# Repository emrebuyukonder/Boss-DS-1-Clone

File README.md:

# Boss DS-1 Distortion Clone (Custom Build) - Outdated

## About The Project

This repository contains the schematic, PCB design files, and build documentation for a custom-built clone of the legendary Boss DS-1 Distortion pedal. Designed from the ground up using **KiCad**, this project aims to faithfully recreate the iconic hard-clipping distortion tone while implementing modern hardware practices such as True Bypass switching and optimized component routing.

## Key Features & Modifications

While the core audio path remains true to the original DS-1 architecture, several mechanical and component-level modifications were made based on the local availability of certain original components and hardware.

* **Custom Transistor Selection:** The original BC549C transistors were substituted with **JC2N3904S49 (NPN)** transistors for the input buffer (Q1), gain boost (Q2), and output buffer (Q3) stages. The PCB footprints were carefully matched to accommodate the E-B-C pinout of the 2N3904.
* **True Bypass Switching:** Unlike the original Boss buffered bypass, this build utilizes a **3PDT 9-Pin Latching Footswitch**. This ensures zero tone coloration when the pedal is disengaged and includes an independent pole for the status LED.
* **Smart Power Management:** Integrated a Stereo Input Jack to act as a ground-shunt switch. The 9V battery is completely disconnected from the circuit when the input cable is unplugged, preserving battery life.
* **Capacitor Accuracy:** High-quality film and ceramic capacitors are used throughout the tone stack and filtering stages (e.g., precise 100pF and 220pF ceramics for RF filtering in the op-amp feedback loop).

## Tools & Technologies Used

* **EDA Software:** KiCad (Schematic Capture & PCB Layout)
* **Testing & Measurement:** UNI-T UT33D+ Digital Multimeter
* **Audio Components:** 1/4" Mono/Stereo Jacks, Custom PCB.

## Hardware Wiring Guide

Proper off-board wiring is critical for a noise-free pedal. Here is the standard implementation used in this build:

* **Input Jack (Stereo):**
   * *Tip:* Routed to 3PDT Switch (Input).
    * *Ring:* Connected to the 9V Battery Negative (Black wire).
    * *Sleeve:* Connected to System Ground (Star Grounding).
* **Output Jack (Mono):**
    * *Tip:* Routed from 3PDT Switch (Output).
    * *Sleeve:* Connected to System Ground.

## Author

Designed and built by **Erdoğan Emre Büyükönder** (Music Producer / Composer under the pseudonym *Magnus Dux*). 

As an Electrical-Electronics Engineering student and a music producer, this project bridges the gap between theoretical circuit analysis and practical, stage-ready audio equipment.

---
*Note: The "Boss" and "DS-1" names are trademarks of Roland Corporation. This project is strictly for educational purposes and personal use.*

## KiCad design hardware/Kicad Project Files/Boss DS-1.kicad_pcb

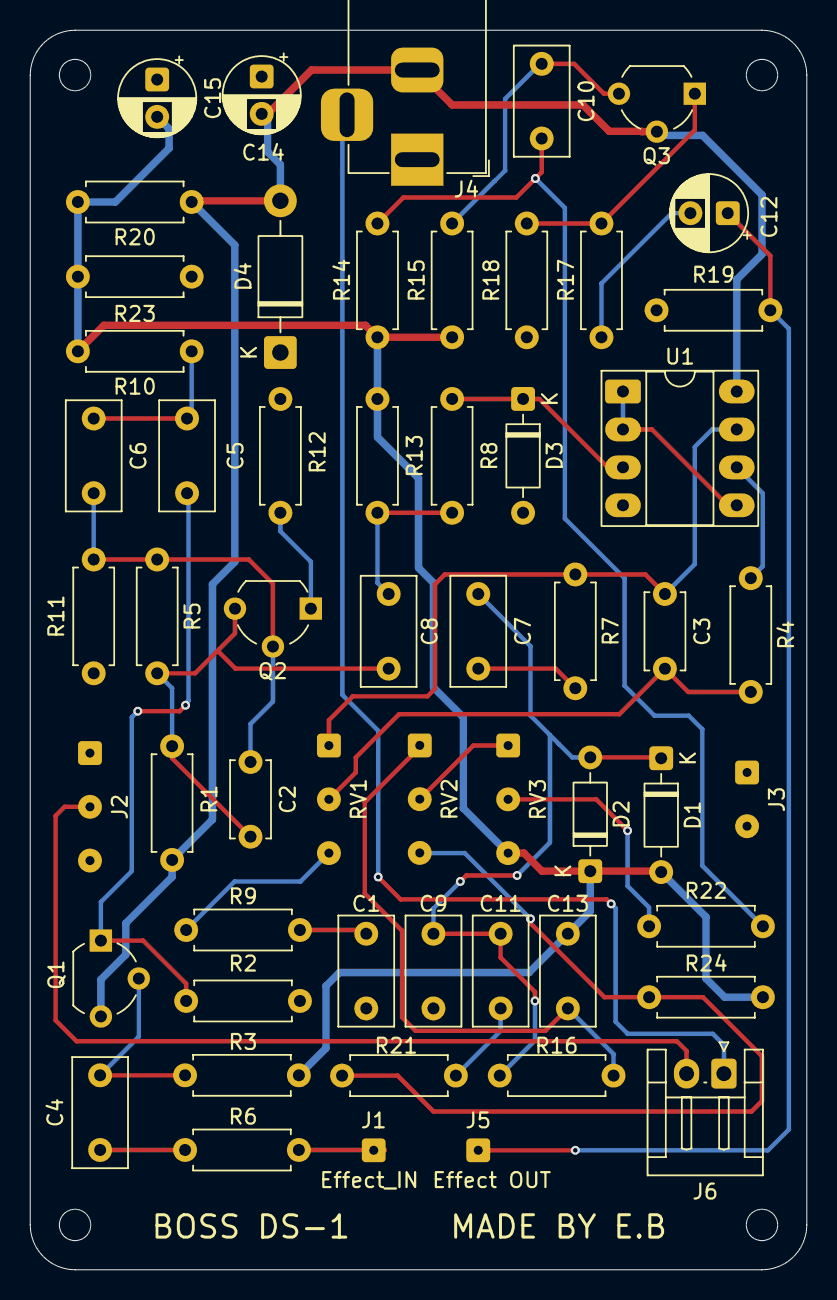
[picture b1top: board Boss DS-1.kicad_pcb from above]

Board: 2 copper layers, 52.0 x 83.0 mm, 56 parts (0 on the bottom side), 33 nets.

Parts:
C1, C5, C7: 0.47u; C_Rect_L7.2mm_W3.5mm_P5.00mm_FKS2_FKP2_MKS2_MKP2
C2: 250p; C_Disc_D5.0mm_W2.5mm_P5.00mm
C3: 100p; C_Disc_D5.0mm_W2.5mm_P5.00mm
C4, C6: 47n; C_Rect_L7.2mm_W3.5mm_P5.00mm_FKS2_FKP2_MKS2_MKP2
C8: 68n; C_Rect_L7.2mm_W3.5mm_P5.00mm_FKS2_FKP2_MKS2_MKP2
C9: 0.01u; C_Rect_L7.2mm_W3.5mm_P5.00mm_FKS2_FKP2_MKS2_MKP2
C10: 0.047u; C_Rect_L7.2mm_W3.5mm_P5.00mm_FKS2_FKP2_MKS2_MKP2
C11: 0.022u; C_Rect_L7.2mm_W3.5mm_P5.00mm_FKS2_FKP2_MKS2_MKP2
C12: 1u; CP_Radial_D5.0mm_P2.50mm
C13: 0.1u; C_Rect_L7.2mm_W3.5mm_P5.00mm_FKS2_FKP2_MKS2_MKP2
C14: 100u; CP_Radial_D5.0mm_P2.50mm
C15: 47u; CP_Radial_D5.0mm_P2.50mm
D1, D2, D3: 1N4148; D_DO-35_SOD27_P7.62mm_Horizontal
D4: 1N4004; D_DO-41_SOD81_P10.16mm_Horizontal
J1: Effect_IN; SolderWire-0.1sqmm_1x01_D0.4mm_OD1mm
J2: INPUT JACK; SolderWire-0.1sqmm_1x03_P3.6mm_D0.4mm_OD1mm
J3: OUTPUT JACK; SolderWire-0.1sqmm_1x02_P3.6mm_D0.4mm_OD1mm
J4: Barrel_Jack_Switch; BarrelJack_Horizontal
J5: Effect OUT; SolderWire-0.1sqmm_1x01_D0.4mm_OD1mm
J6: 9V Battery; JST_EH_S2B-EH_1x02_P2.50mm_Horizontal
Q1, Q2: 2N3904; TO-92_Wide
Q3: 2SC2240; TO-92_Wide
R1, R9, R18, R20, R22, R23: 10k; R_Axial_DIN0207_L6.3mm_D2.5mm_P7.62mm_Horizontal
R2: 4.7k; R_Axial_DIN0207_L6.3mm_D2.5mm_P7.62mm_Horizontal
R3, R5: 470k; R_Axial_DIN0207_L6.3mm_D2.5mm_P7.62mm_Horizontal
R4, R10, R11, R13, R19: 100k; R_Axial_DIN0207_L6.3mm_D2.5mm_P7.62mm_Horizontal
R6, R17: 1k; R_Axial_DIN0207_L6.3mm_D2.5mm_P7.62mm_Horizontal
R7, R21: 2.2k; R_Axial_DIN0207_L6.3mm_D2.5mm_P7.62mm_Horizontal
R8: 47k; R_Axial_DIN0207_L6.3mm_D2.5mm_P7.62mm_Horizontal
R12: 22; R_Axial_DIN0207_L6.3mm_D2.5mm_P7.62mm_Horizontal
R14, R15: 1M; R_Axial_DIN0207_L6.3mm_D2.5mm_P7.62mm_Horizontal
R16, R24: 6.8k; R_Axial_DIN0207_L6.3mm_D2.5mm_P7.62mm_Horizontal
RV1, RV3: 100kB; SolderWire-0.1sqmm_1x03_P3.6mm_D0.4mm_OD1mm
RV2: 20kB; SolderWire-0.1sqmm_1x03_P3.6mm_D0.4mm_OD1mm
U1: TL072; DIP-8_W7.62mm_Socket_LongPads

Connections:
+9V: C14.2, D4.2 (A), J4.2, Q1.3 (C), Q3.2 (C), R1.1, R20.1, U1.8 (V+)
/+4.5V: C13.1, C15.2, D1.2 (A), D2.1 (K), R3.2, R10.2, R13.2, R14.1, R15.1, R20.2, R23.1, R24.2, RV3.3
/BAT_NEG: J2.2, J6.2
/Effect_IN: J1.1, R6.1
/Effect_OUT: C12.1, J5.1, R19.2
/Opamp_Gain: C7.2, C9.1, C11.2, D1.1 (K), D2.2 (A), R16.1
/Tone_Level: C10.2, R14.2, R22.2
/Trans_boost: C2.2, C8.1, Q2.3 (C), R1.2, R5.2
/input_buff: C5.1, Q1.1 (E), R9.1
GND: C1.1, C9.2, C14.1, C15.1, D3.2 (A), D4.1 (K), J2.3, J3.2, J4.1, R9.2, R11.2, R12.2, R18.1, R19.1, R23.2, U1.4 (V-)
unnamed: C1.2, R2.2
unnamed: C3.1, R7.1, RV1.1, U1.7
unnamed: C3.2, R4.2, RV1.2
unnamed: C4.1, R6.2
unnamed: C5.2, C6.1, R10.1
unnamed: C7.1, R7.2
unnamed: C8.2, R8.1, R13.1
unnamed: C11.1, R21.1
unnamed: C12.2, R17.1
unnamed: C13.2, R16.2, RV2.1
unnamed: D3.1 (K), R8.2, U1.3 (+)
unnamed: J4.3, J6.1
unnamed: C4.2, Q1.2 (B), R3.1
unnamed: C2.1, C6.2, Q2.2 (B), R5.1, R11.1
unnamed: Q2.1 (E), R12.1
unnamed: C10.1, Q3.3 (B), R15.2
unnamed: Q3.1 (E), R17.2, R18.2
unnamed: R2.1, RV1.3
unnamed: R21.2, R24.1, RV2.3
unnamed: R22.1, RV3.2
unnamed: RV2.2, RV3.1
unnamed: U1.1, U1.2 (-), U1.5 (+)
unnamed: R4.1, U1.6 (-)

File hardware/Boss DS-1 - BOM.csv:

"Reference","Qty","Value","DNP","Exclude from BOM","Exclude from Board","Footprint","Datasheet"
"U1","1","TL072","","","","Package_DIP:DIP-8_W7.62mm_Socket_LongPads","http://www.ti.com/lit/ds/symlink/tl071.pdf"
"SW1","1","SW_Slide_DPDT","","","","","~"
"RV2","1","20kB","","","","Connector_Wire:SolderWire-0.1sqmm_1x03_P3.6mm_D0.4mm_OD1mm","~"
"RV1,RV3","2","100kB","","","","Connector_Wire:SolderWire-0.1sqmm_1x03_P3.6mm_D0.4mm_OD1mm","~"
"R16,R24","2","6.8k","","","","Resistor_THT:R_Axial_DIN0207_L6.3mm_D2.5mm_P7.62mm_Horizontal","~"
"R14,R15","2","1M","","","","Resistor_THT:R_Axial_DIN0207_L6.3mm_D2.5mm_P7.62mm_Horizontal","~"
"R12","1","22","","","","Resistor_THT:R_Axial_DIN0207_L6.3mm_D2.5mm_P7.62mm_Horizontal","~"
"R8","1","47k","","","","Resistor_THT:R_Axial_DIN0207_L6.3mm_D2.5mm_P7.62mm_Horizontal","~"
"R7,R21","2","2.2k","","","","Resistor_THT:R_Axial_DIN0207_L6.3mm_D2.5mm_P7.62mm_Horizontal","~"
"R6,R17","2","1k","","","","Resistor_THT:R_Axial_DIN0207_L6.3mm_D2.5mm_P7.62mm_Horizontal","~"
"R4,R10,R11,R13,R19","5","100k","","","","Resistor_THT:R_Axial_DIN0207_L6.3mm_D2.5mm_P7.62mm_Horizontal","~"
"R3,R5","2","470k","","","","Resistor_THT:R_Axial_DIN0207_L6.3mm_D2.5mm_P7.62mm_Horizontal","~"
"R2","1","4.7k","","","","Resistor_THT:R_Axial_DIN0207_L6.3mm_D2.5mm_P7.62mm_Horizontal","~"
"R1,R9,R18,R20,R22,R23","6","10k","","","","Resistor_THT:R_Axial_DIN0207_L6.3mm_D2.5mm_P7.62mm_Horizontal","~"
"Q1,Q2,Q3","3","2N3904","","","","Package_TO_SOT_THT:TO-92_Wide","https://media.digikey.com/pdf/Data%20Sheets/Toshiba%20PDFs/2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"
"J6","1","9V Battery","","","","Connector_JST:JST_EH_S2B-EH_1x02_P2.50mm_Horizontal","~"
"J5","1","Effect OUT","","","","Connector_Wire:SolderWire-0.1sqmm_1x01_D0.4mm_OD1mm","~"
"J4","1","Barrel_Jack_Switch","","","","Connector_BarrelJack:BarrelJack_Horizontal","~"
"J3","1","OUTPUT JACK","","","","Connector_Wire:SolderWire-0.1sqmm_1x02_P3.6mm_D0.4mm_OD1mm","~"
"J2","1","INPUT JACK","","","","Connector_Wire:SolderWire-0.1sqmm_1x03_P3.6mm_D0.4mm_OD1mm","~"
"J1","1","Effect_IN","","","","Connector_Wire:SolderWire-0.1sqmm_1x01_D0.4mm_OD1mm","~"
"D4","1","1N4004","","","","Diode_THT:D_DO-41_SOD81_P10.16mm_Horizontal","~"
"D1,D2,D3","3","1N4148","","","","Diode_THT:D_DO-35_SOD27_P7.62mm_Horizontal","~"
"C15","1","47u","","","","Capacitor_THT:CP_Radial_D5.0mm_P2.50mm","~"
"C14","1","100u","","","","Capacitor_THT:CP_Radial_D5.0mm_P2.50mm","~"
"C13","1","0.1u","","","","Capacitor_THT:C_Rect_L7.2mm_W3.5mm_P5.00mm_FKS2_FKP2_MKS2_MKP2","~"
"C12","1","1u","","","","Capacitor_THT:CP_Radial_D5.0mm_P2.50mm","~"
"C11","1","0.022u","","","","Capacitor_THT:C_Rect_L7.2mm_W3.5mm_P5.00mm_FKS2_FKP2_MKS2_MKP2","~"
"C10","1","0.047u","","","","Capacitor_THT:C_Rect_L7.2mm_W3.5mm_P5.00mm_FKS2_FKP2_MKS2_MKP2","~"
"C9","1","0.01u","","","","Capacitor_THT:C_Rect_L7.2mm_W3.5mm_P5.00mm_FKS2_FKP2_MKS2_MKP2","~"
"C8","1","68n","","","","Capacitor_THT:C_Rect_L7.2mm_W3.5mm_P5.00mm_FKS2_FKP2_MKS2_MKP2","~"
"C4,C6","2","47n","","","","Capacitor_THT:C_Rect_L7.2mm_W3.5mm_P5.00mm_FKS2_FKP2_MKS2_MKP2","~"
"C3","1","100p","","","","Capacitor_THT:C_Disc_D5.0mm_W2.5mm_P5.00mm","~"
"C2","1","250p","","","","Capacitor_THT:C_Disc_D5.0mm_W2.5mm_P5.00mm","~"
"C1,C5,C7","3","0.47u","","","","Capacitor_THT:C_Rect_L7.2mm_W3.5mm_P5.00mm_FKS2_FKP2_MKS2_MKP2","~"

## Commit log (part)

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2026-05-17 All the files necessary to build this project has been added.
2026-05-17 Revise README for Boss DS-1 Distortion Clone
    Expanded project details, features, and author information in README.
2026-05-17 Update 1
2026-05-17 Update 2
2026-06-02 updates and cleanup
2026-06-02 Remove status badge from README
    Removed status badge indicating project completion.
